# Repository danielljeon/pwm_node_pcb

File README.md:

# pwm_node_pcb

PCB for CAN-controlled PWM controller.

- Firmware: [`pwm_node`](https://github.com/danielljeon/pwm_node).

---

<details markdown="1">
  <summary>Table of Contents</summary>

<!-- TOC -->
* [pwm_node_pcb](#pwm_node_pcb)
  * [1 Overview](#1-overview)
  * [2 Board Specifications](#2-board-specifications)
    * [2.1 Connectors](#21-connectors)
    * [2.2 Switches & Jumpers](#22-switches--jumpers)
  * [3 Release Notes](#3-release-notes)
    * [3.1 v0.1.0-alpha](#31-v010-alpha)
<!-- TOC -->

</details>

---

## 1 Overview

|                        Top                         |                          Bottom                          |
|:--------------------------------------------------:|:--------------------------------------------------------:|
|  |  |

---

## 2 Board Specifications

### 2.1 Connectors

Connectors fixed by hardware (PCB traces or the connector itself).

| Connector             | Ref | Description                                          |
|-----------------------|:---:|------------------------------------------------------|
| Battery (input)       | J1  | Battery supply input                                 |
| 5 V Breakout (output) | J3  | 5 V output from buck converter                       |
| Tag-Connect TC2050    | J3  | Programming/debug connector                          |
| V Load (input)        | J4  | Load supply input                                    |
| 4x Load connectors    | J5  | Pin row 1: PWM, Pin row 2: V Load, Pin row 3: Ground |
| CAN1                  | J6  | Pin 1: CAN1 High, Pin 2: CAN1 Low                    |
| MCU NRESET jumper     | JP1 | Short to reset                                       |

### 2.2 Switches & Jumpers

User controllable hardware and/or firmware driven inputs.

| Switch/Jumper | Ref | Description                                          |
|---------------|:---:|------------------------------------------------------|
| BOOT0 jumper  | JP2 | Open for run flash memory (pull-down on open)        |
| Test pad 1    | TP1 | 1.5 mm diameter test pad, chosen for `PB6` (UART TX) |
| Test pad 2    | TP2 | 1.5 mm diameter test pad, chosen for `PB7` (UART RX) |

---

## 3 Release Notes

### 3.1 v0.1.0-alpha

- Pre-release 4-layer board variant.
    - Short-term pre-release board bring-up/testing release.
- Order date: 2025/04/29.

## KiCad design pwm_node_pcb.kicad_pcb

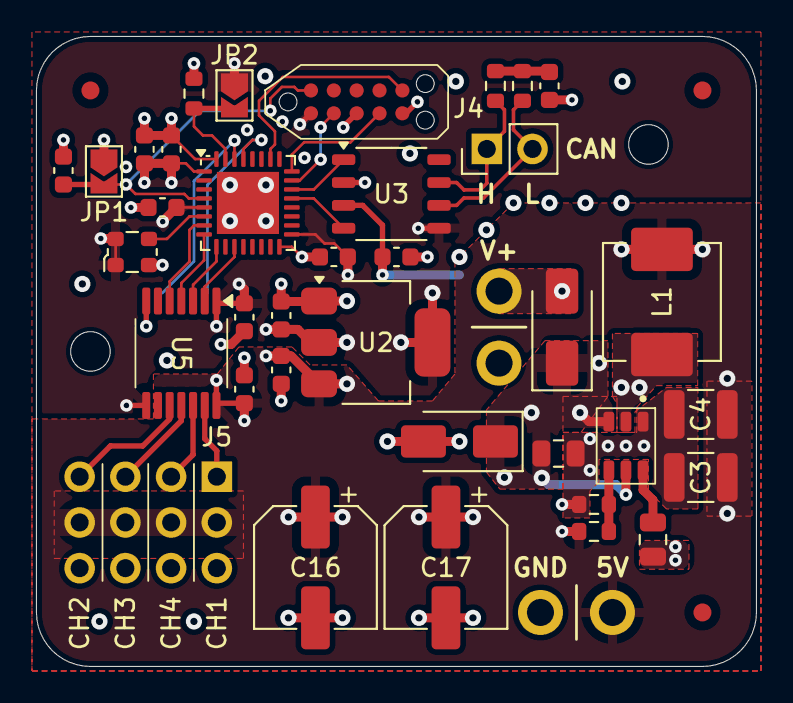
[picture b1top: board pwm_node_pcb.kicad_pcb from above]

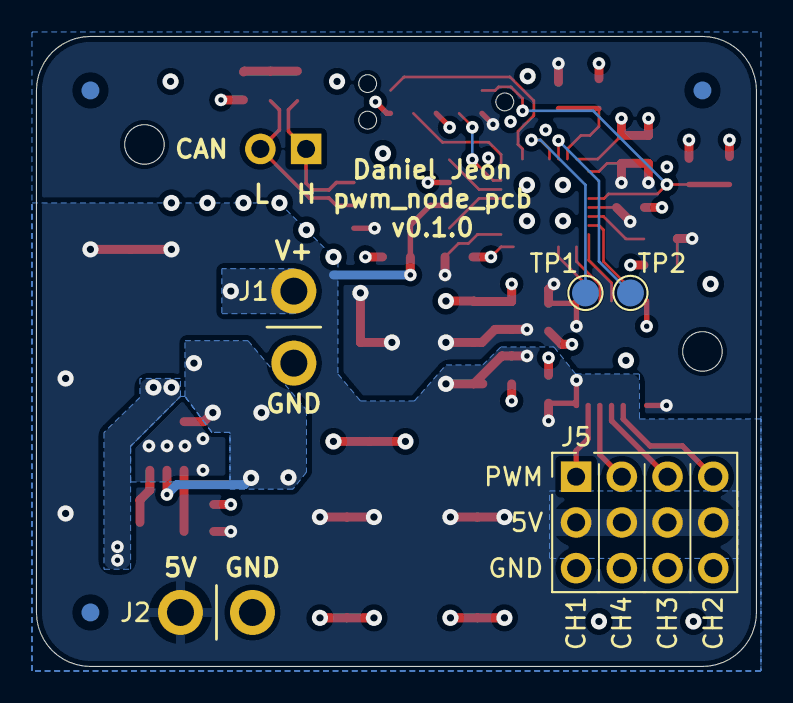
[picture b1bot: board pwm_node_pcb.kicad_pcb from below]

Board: 4 copper layers, 40.0 x 35.0 mm, 48 parts (8 on the bottom side), 29 nets.

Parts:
C1: 100n; C_0805_2012Metric
C2: 2u2; C_0805_2012Metric
C3, C4: 22u; C_1210_3225Metric
C5, C7, C8, C9, C10, C12, C14, C15: 100n; C_0603_1608Metric
C6: 10u; C_0603_1608Metric
C11: 4u7; C_0603_1608Metric
C13: 4n7; C_0603_1608Metric
C16, C17: 220u; CP_Elec_6.3x5.2
D1: SK36A-LTP; D_SMA
D2: SMAJ15A-13-F; D_SMA
FM1, FM2, FM3, FM4, FM5, FM6: 1mm; Fiducial_1mm_Mask2mm
H1, H2: M2; MountingHole_2.2mm_M2
J1: Battery; battery
J2: 5V Breakout; battery
J3: TC2050-IDC-NL; tag_connect_tc2050-idc-nl
J4: CAN1; PinHeader_1x02_P2.54mm_Vertical
J5: 3x4_2-54mm_breakout
JP1, JP2: Open; SolderJumper-2_P1.3mm_Open_TrianglePad1.0x1.5mm
L1: 6u8; vishay_ihlp-2525cz
R1: 100k; R_0603_1608Metric
R2: 13k7; R_0603_1608Metric
R3, R4: 60R; R_0603_1608Metric
R5: 10k; R_0603_1608Metric
TP1: UART_TX; TestPoint_Pad_D1.5mm
TP2: UART_RX; TestPoint_Pad_D1.5mm
U1: LMR51430; lmr51430
U2: LD1117S33CTR; SOT-223-3_TabPin2
U3: TJA1051T/3; sot96-1_soic-8
U4: STM32L432KCU; QFN-32-1EP_5x5mm_P0.5mm_EP3.45x3.45mm
U5: TXB0104QPWRQ1; txb0104qpwrq1
Y1: ECS-2520MV-080-BN; Oscillator_SMD_ECS_2520MV-xxx-xx-4Pin_2.5x2.0mm

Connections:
+3V3: C6.1, C8.1, C9.1, C10.1, C11.1, C14.1, J3.1 (VCC), JP2.1 (A), U2.2 (VO), U3.5 (V_{IO}), U4.1 (VDD), U4.5 (VDDA), U4.17 (VDD), U5.1 (V_{CCA}), U5.8 (OE), Y1.1 (Tri-State), Y1.4 (VDD)
+5V: C3.2, C4.2, C5.1, C7.1, C15.1, C16.1, C17.1, J2.1, J5.2, J5.5, J5.8, J5.11, L1.2, R1.2, U2.3 (VI), U3.3 (V_{CC}), U5.14 (V_{CCB})
+VSUPPLY: C2.1, D1.1 (K), D2.1 (A1), U1.3 (VIN), U1.5 (EN)
/BOOT0: JP2.2 (B), R5.1, U4.31 (BOOT0)
/BUCK_SW: C1.2, L1.1, U1.2 (SW)
/CAN1+: J4.1, R4.1, U3.7 (CANH)
/CAN1-: J4.2, R3.1, U3.6 (CANL)
/CAN1_RX: U3.4 (RXD), U4.21 (PA11)
/CAN1_TX: U3.1 (TXD), U4.22 (PA12)
/NRST: C12.2, J3.10 (~RESET), JP1.2 (B), U4.4 (NRST)
/PWM1_{5V}: J5.1, U5.13 (B1)
/PWM2_{5V}: J5.10, U5.10 (B4)
/PWM3_{5V}: J5.7, U5.11 (B3)
/PWM4_{5V}: J5.4, U5.12 (B2)
/SWCLK: J3.4 (SWCLK/TCK), U4.24 (PA14)
/SWDIO: J3.2 (SWDIO/TMS), U4.23 (PA13)
/SWO: J3.6 (SWO/TDO), U4.26 (PB3)
/TIM1_CH1: U4.11 (PA5), U5.2 (A1)
/TIM1_CH2: U4.7 (PA1), U5.5 (A4)
/TIM1_CH3: U4.8 (PA2), U5.4 (A3)
/TIM1_CH4: U4.9 (PA3), U5.3 (A2)
/USART1_RX: TP2.1, U4.30 (PB7)
/USART1_TX: TP1.1, U4.29 (PB6)
GND: C2.2, C3.1, C4.1, C5.2, C6.2, C7.2, C8.2, C9.2, C10.2, C11.2, C12.1, C13.2, C14.2, C15.2, C16.2, C17.2, D2.2 (A2), J1.2, J2.2, J3.3 (GND), J3.5 (GND/VPROG), J5.3, J5.6, J5.9, J5.12, JP1.1 (A), R2.2, R5.2, U1.1 (GND), U2.1 (GND), U3.2 (GND), U4.16 (VSS), U4.32 (VSS), U4.33 (VSS), U5.7 (GND), Y1.2 (GND)
unnamed: C13.1, R3.2, R4.2
unnamed: D1.2 (A), J1.1
unnamed: C1.1, U1.6 (CB)
unnamed: R1.1, R2.1, U1.4 (FB)
unnamed: U4.6 (PA0), Y1.3 (OUT)

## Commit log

2025-01-03 Add .gitignore
2025-01-03 Add component_library submodule
2025-01-03 Add missed partial component_library submodule
2025-01-03 Add CODEOWNERS
2025-01-05 Add config.kibot.yaml
2025-01-05 Add WIP passing ERC DRC
2025-01-25 Add re-layout WIP changes
2025-01-27 Cleanup layout and routing
2025-01-27 Add KiBot workflow file
2025-04-24 Update component library
2025-04-24 Fix component libraries
2025-04-24 Revamp schematic and nuke PCB
2025-04-24 Initial component placement
2025-04-24 Split load supply and rough placement
2025-04-24 Pass ERC and DRC, initial v0.1.0-alpha
2025-04-24 Fix old broken footprints
2025-04-24 Update KiBot workflow for KiCad 9
2025-04-24 Add version silkscreen and update pictures
2025-04-28 Add minor decoupling caps, board cleanup
2025-04-28 Trace cleanup
2025-04-28 Add TVS and schottky diodes
2025-04-29 Add GND plane stitching vias
2025-04-29 Add testpads/UART breakout
2025-04-29 Update README.md for v0.1.0-alpha release
2025-04-29 Fix silkscreen and load caps to 220uF
2025-05-08 Fix flipped UART breakout (TP) nets
2025-05-08 Fix level shifter circuit
2025-05-09 Update sch and pcb sheet info
2025-05-10 Fix load cap fp and remove dedicated supply
2025-05-12 Minimize use of inpad vias
2025-05-14 Update README.md for PCB-firmware references
2025-05-14 Add TVS and schottky diode info
2025-05-27 Fix missing outer layer non-functional pads (vias)
2025-06-03 Update config.kibot.yaml for KiCad/Bot 9
